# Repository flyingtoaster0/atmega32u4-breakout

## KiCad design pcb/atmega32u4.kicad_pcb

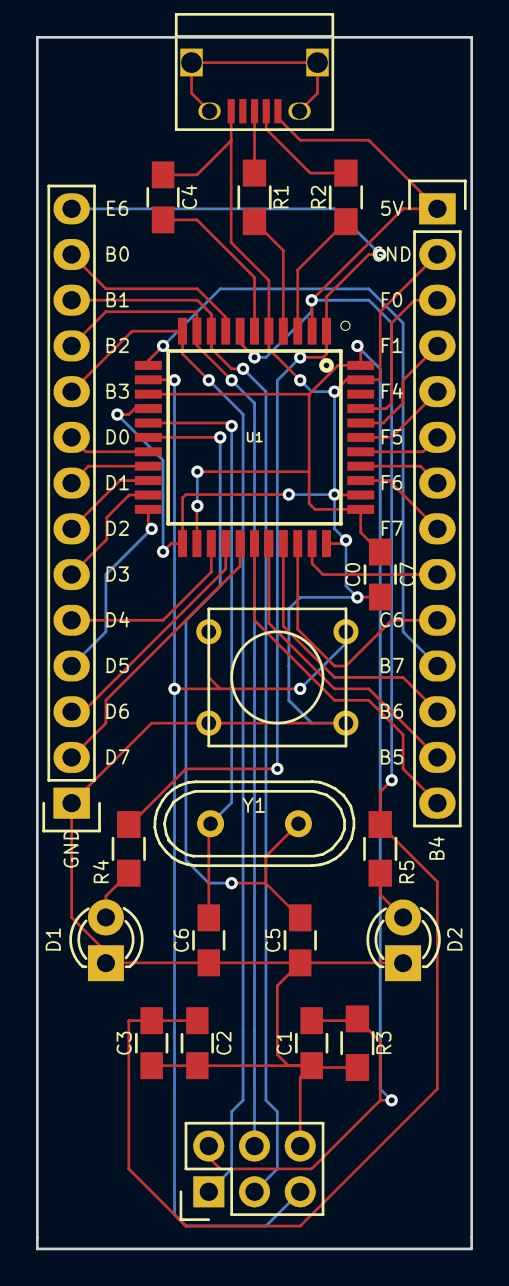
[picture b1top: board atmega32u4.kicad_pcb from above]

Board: 2 copper layers, 24.1 x 67.3 mm, 21 parts (0 on the bottom side), 38 nets.

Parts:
C0: C0; C_0805_HandSoldering
C1: C1; C_0805_HandSoldering
C2: C2; C_0805_HandSoldering
C3: C3; C_0805_HandSoldering
C4: C4; C_0805_HandSoldering
C5: C5; C_0805_HandSoldering
C6: C6; C_0805_HandSoldering
CON1: ISP; Pin_Header_Straight_2x03
D1: D1; LED-3MM
D2: D2; LED-3MM
P1, P2: CONN_01X14; Pin_Header_Straight_1x14
P3: USB_OTG; USB_Micro-B
R1: R1; R_0805_HandSoldering
R2: R2; R_0805_HandSoldering
R3: R3; R_0805_HandSoldering
R4: R4; R_0805_HandSoldering
R5: R5; R_0805_HandSoldering
SW1: SW_PUSH; SW_PUSH_SMALL
U1: U1; QFP80P1200X1200X120-44N
Y1: Y1; Crystal_HC49-U_Vertical

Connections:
+5V: C2.1, C3.1, P1.1, P3.1, R5.1, U1.2, U1.7
/ISP_MISO/PB3: CON1.1, P2.10, U1.11
/ISP_MOSI/PB2: CON1.4, P2.11, U1.10
/ISP_RESET: CON1.5, SW1.1, U1.13
/ISP_SCK/PB1: CON1.3, P2.12, U1.9
/PB0: P2.13, U1.8
/PB4: P1.14, U1.28
/PB5: P1.13, U1.29
/PB6: P1.12, U1.30
/PB7: P1.11, U1.12
/PC6: P1.10, U1.31
/PC7: P1.9, U1.32
/PD0: P2.9, U1.18
/PD1: P2.8, U1.19
/PD2: P2.7, U1.20
/PD3: P2.6, U1.21
/PD4: P2.5, U1.25
/PD5: P2.4, U1.22
/PD6: P2.3, U1.26
/PD7: P2.2, U1.27
/PE6: P2.14, R4.1, U1.1
/PF0: P1.3, U1.41
/PF1: P1.4, U1.40
/PF4: P1.5, U1.39
/PF5: P1.6, U1.38
/PF6: P1.7, U1.37
/PF7: P1.8, U1.36
/XTAL1: C5.1, U1.17, Y1.1
/XTAL2: C6.1, U1.16, Y1.2
GND: C0.2, C1.2, C2.2, C3.2, C4.2, C5.2, C6.2, CON1.6, D1.1, D2.1, P1.2, P2.1, P3.5, R3.2, SW1.2, U1.5, U1.15, U1.23, U1.33, U1.35, U1.43
unnamed: C4.1, U1.6
unnamed: D1.2, R4.2
unnamed: D2.2, R5.2
unnamed: P3.2, R2.2
unnamed: P3.3, R1.2
unnamed: R1.1, U1.4
unnamed: R2.1, U1.3
VCC: C0.1, C1.1, CON1.2, R3.1, U1.14, U1.24, U1.34, U1.44

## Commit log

2016-09-19 Start work on schematic
2016-09-19 Add crystal, connectors
2016-09-19 Remove .bak file
2016-09-21 Complete schematic
2016-09-21 Associated footprints
2016-09-21 Fix up CONN labels on schematic
2016-09-21 Start some work on the pcb
2016-09-23 Hook up most of the left side
2016-09-23 Finish left side and programming header
2016-09-23 Commit before cleanup
2016-09-23 jk I didn’t do cleanup. I finished the connections
2016-09-28 Add outline to board
2016-09-28 Fix up schematic accoring to adafruit
2016-09-28 Rearrange pins
2016-09-28 Add LEDs
2016-09-28 Update net
2016-09-28 Update footprints
2016-09-28 about to rewire pcb
2016-09-28 About to do bottom layer
2016-09-28 I think I'm done?
2016-09-28 add edge cuts
2016-09-28 Finished dat board
2016-11-10 something
2016-11-25 Relabel components
2016-11-25 change oval holds to circular
